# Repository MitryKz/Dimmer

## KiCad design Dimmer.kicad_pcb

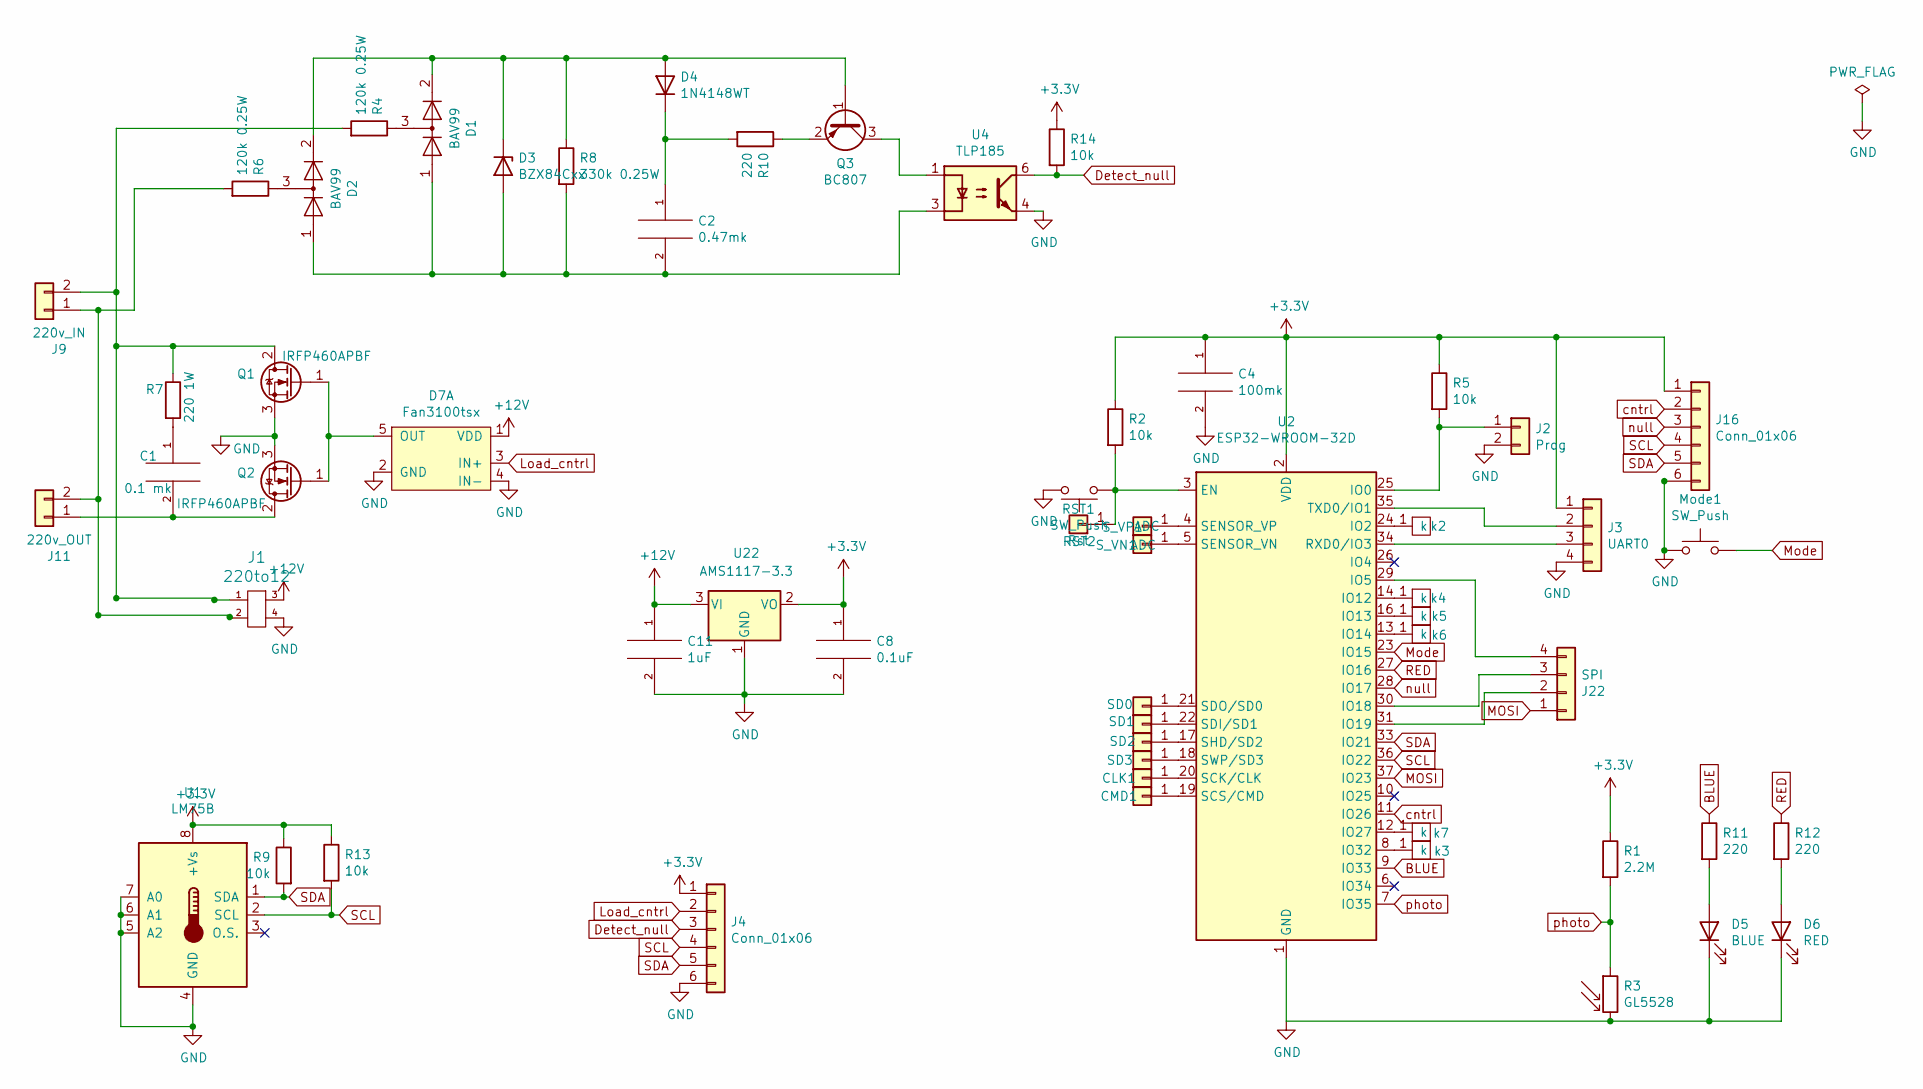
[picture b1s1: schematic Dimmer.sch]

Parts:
C1: 0.1 mk; C_Rect_L10.0mm_W2.5mm_P7.50mm_MKS4
C2: 0.47mk; C_0805_2012Metric
C4: 100mk; C_0805_2012Metric
C8: 0.1uF; C_0805_2012Metric
C11: 1uF; C_0805_2012Metric
CLK1: Pin; polz_razjem
CMD1: Pin; polz_razjem
D1, D2: BAV99; SOT-23
D3: BZX84Cxx; D_SOT-23_ANK
D4: 1N4148WT; D_SOD-123
D5: BLUE; LED_0805_2012Metric
D6: RED; LED_0805_2012Metric
D7: Fan3100tsx; SOT-23-5
J1: 220to12; oblast_bp
J2: Prog; 2pins
J3: UART0; 4pins
J4, J16: Conn_01x06; PinHeader_1x06_P2.54mm_Vertical
J9: 220v_IN; OUT_IN(1)
J11: 220v_OUT; OUT_IN(1)
J22: SPI; PinHeader_1x04_P2.54mm_Vertical
Mode1: SW_Push; aLIEXPRESS_BUTTON_G71Y
Q1, Q2: IRFP460APBF; TO-247-3_Horizontal_TabDown
Q3: BC807; SOT-23
R1: 2.2M; R_0805_2012Metric
R2, R5, R9, R13, R14: 10k; R_0805_2012Metric
R3: GL5528; R_LDR_5.1x4.3mm_P3.4mm_Vertical
R4, R6: 120k 0.25W; R_0805_2012Metric
R7: 220 1W; R_2512_6332Metric
R8: 330k 0.25W; R_0805_2012Metric
R10, R11, R12: 220; R_0805_2012Metric
RST1: Rst; polz_razjem
RST2: SW_Push; aLIEXPRESS_BUTTON_G71Y
SD0, SD1, SD2, SD3: Pin; polz_razjem
S_VN1: ADC; polz_razjem
S_VP1: ADC; polz_razjem
U1: LM75B; Diodes_SO-8
U2: ESP32-WROOM-32D; ESP32-WROOM-32
U4: TLP185; SOIC-4_4.55x3.7mm_P2.54mm
U22: AMS1117-3.3; SOT-223-3_TabPin2
k2, k3, k4, k5, k6, k7: Key; TestPoint_Pad_1.0x1.0sm

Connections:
+3V3: C4.1, C8.1, J3.1, J4.1, J16.1, R1.1, R2.1, R5.1, R9.1, R13.1, R14.1, U1.8 (+Vs), U2.2 (VDD), U22.2 (VO)
+12V: C11.1, D7.1 (VDD), J1.3, U22.3 (VI)
BLUE: R11.1, U2.9 (IO33)
Detect_null: J4.3, R14.2, U4.6
GND: C4.2, C8.2, C11.2, D5.1 (K), D6.1 (K), D7.2 (GND), D7.4 (IN-), J1.4, J2.2, J3.4, J4.6, J16.6, Mode1.1, Q1.3 (S), Q2.3 (S), R3.2, RST2.2, U1.4 (GND), U1.5 (A2), U1.6 (A1), U1.7 (A0), U2.1 (GND), U2.15 (GND), U2.38 (GND), U2.39 (GND), U4.4, U22.1 (GND)
Load_cntrl: D7.3 (IN+), J4.2
MOSI: J22.1, U2.37 (IO23)
Mode: Mode1.2, U2.23 (IO15)
unnamed: C1.1, R7.2
unnamed: C1.2, J11.1, Q2.2 (D)
unnamed: C2.1, D4.1 (K), R10.2
unnamed: C2.2, D1.1 (K), D2.1 (K), D3.2 (A), R8.2, U4.3
unnamed: CLK1.1, U2.20 (SCK/CLK)
unnamed: CMD1.1, U2.19 (SCS/CMD)
unnamed: D1.2 (A), D2.2 (A), D3.1 (K), D4.2 (A), Q3.1 (B), R8.1
unnamed: D1.3 (K), R4.1
unnamed: D2.3 (K), R6.1
unnamed: D5.2 (A), R11.2
unnamed: D6.2 (A), R12.2
unnamed: D7.5 (OUT), Q1.1 (G), Q2.1 (G)
unnamed: J1.1, J9.2, Q1.2 (D), R4.2, R7.1
unnamed: J1.2, J9.1, J11.2, R6.2
unnamed: J2.1, R5.2, U2.25 (IO0)
unnamed: J3.2, U2.35 (TXD0/IO1)
unnamed: J3.3, U2.34 (RXD0/IO3)
unnamed: J22.2, U2.31 (IO19)
unnamed: J22.3, U2.30 (IO18)
unnamed: J22.4, U2.29 (IO5)
unnamed: Q3.2 (E), R10.1
unnamed: Q3.3 (C), U4.1
unnamed: R2.2, RST1.1, RST2.1, U2.3 (EN)
unnamed: SD0.1, U2.21 (SDO/SD0)
unnamed: SD1.1, U2.22 (SDI/SD1)
unnamed: SD2.1, U2.17 (SHD/SD2)
unnamed: SD3.1, U2.18 (SWP/SD3)
unnamed: S_VN1.1, U2.5 (SENSOR_VN)
unnamed: S_VP1.1, U2.4 (SENSOR_VP)
unnamed: U2.8 (IO32), k3.1
unnamed: U2.12 (IO27), k7.1
unnamed: U2.13 (IO14), k6.1
unnamed: U2.14 (IO12), k4.1
unnamed: U2.16 (IO13), k5.1
unnamed: U2.24 (IO2), k2.1
RED: R12.1, U2.27 (IO16)
SCL: J4.4, J16.4, R13.2, U1.2 (SCL), U2.36 (IO22)
SDA: J4.5, J16.5, R9.2, U1.1 (SDA), U2.33 (IO21)
cntrl: J16.2, U2.11 (IO26)
null: J16.3, U2.28 (IO17)
photo: R1.2, R3.1, U2.7 (IO35)

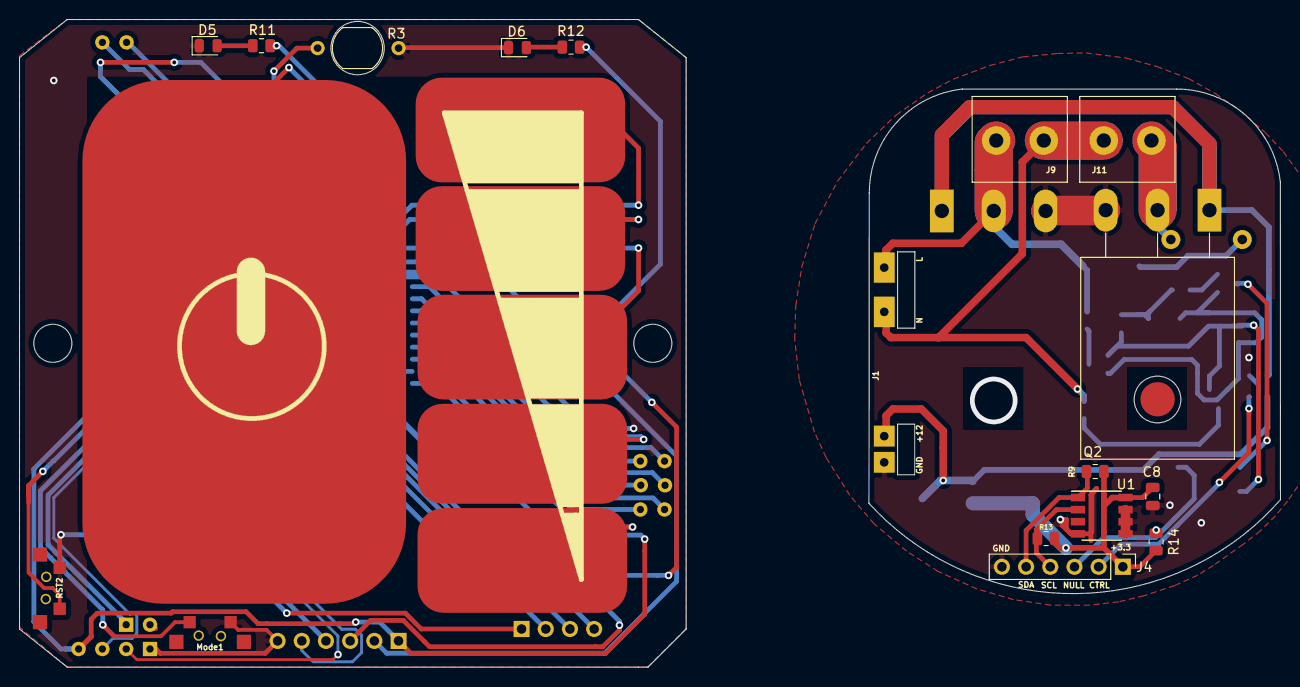
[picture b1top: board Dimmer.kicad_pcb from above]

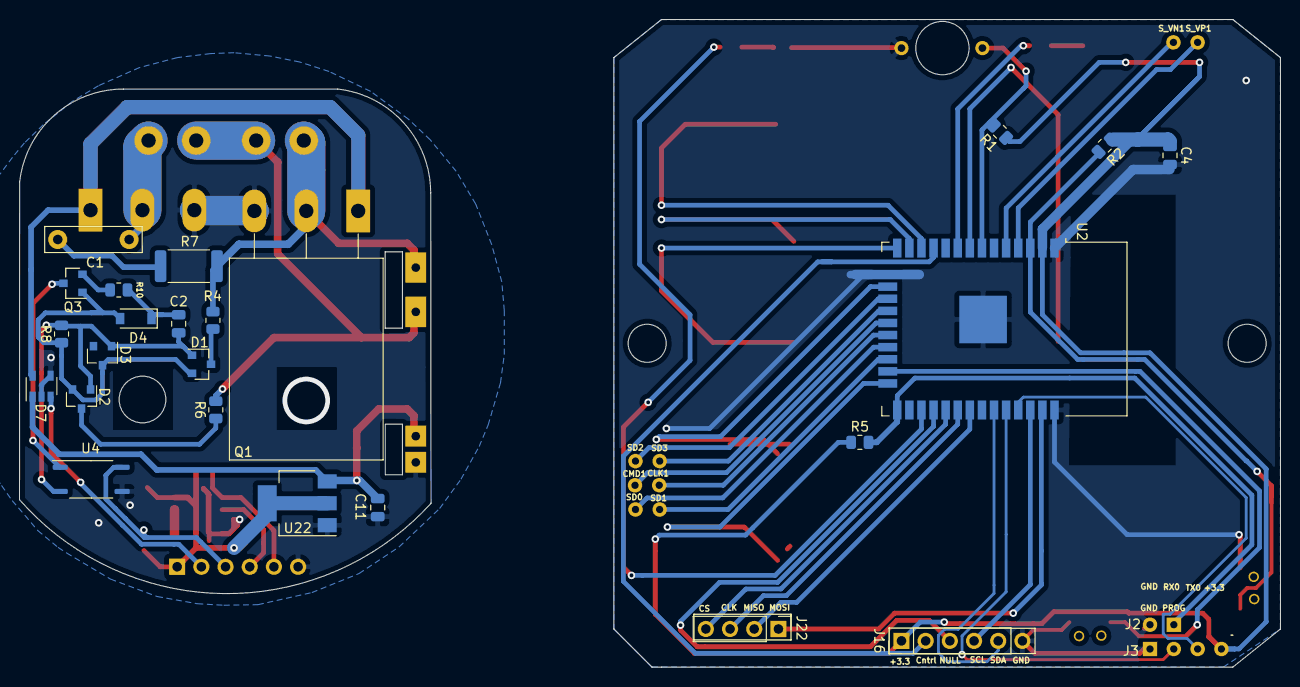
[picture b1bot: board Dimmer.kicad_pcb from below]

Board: 2 copper layers, 132.4 x 68.0 mm, 57 parts (28 on the bottom side), 49 nets.

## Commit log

2021-08-11 New regulator, buttons
2021-08-14 Ordered
    Sensor solder mask fix
2021-10-14 Заменены посадочные места, переразведена нижняя плата
2021-10-14 Добавлены С1 и R7
2021-10-23 Замена С1, блок 220-12 поставлен вертикально
2021-10-25 Замена кнопок
2021-11-10 Поправлена шелкография, заказ V3
